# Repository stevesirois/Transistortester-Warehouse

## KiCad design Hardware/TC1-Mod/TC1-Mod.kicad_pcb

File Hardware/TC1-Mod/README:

------------------------------------------------------------------------------

  Modification for Multifunction Tester TC-1

  (c) 2018 by Markus Reschke (madires@theca-tabellaria.de)

------------------------------------------------------------------------------

The TC-1 Transistor Tester clone uses an additional small MCU for controlling
the power supply causing an incompatibilty with the open source k and
m-firmware. This small circuit is meant to replace the control MCU U4 to
be able to run the open source firmware. I'd recommend to glue the tiny
PCB of the replacement circuit to the main PCB using hot glue, and to connect
U4's pads with thin enamel wire (magnet wire). Please see the included
pictures for an inspiration ;)

PS: Remove the Li-Ion battery during the modifaction to prevent any damage.

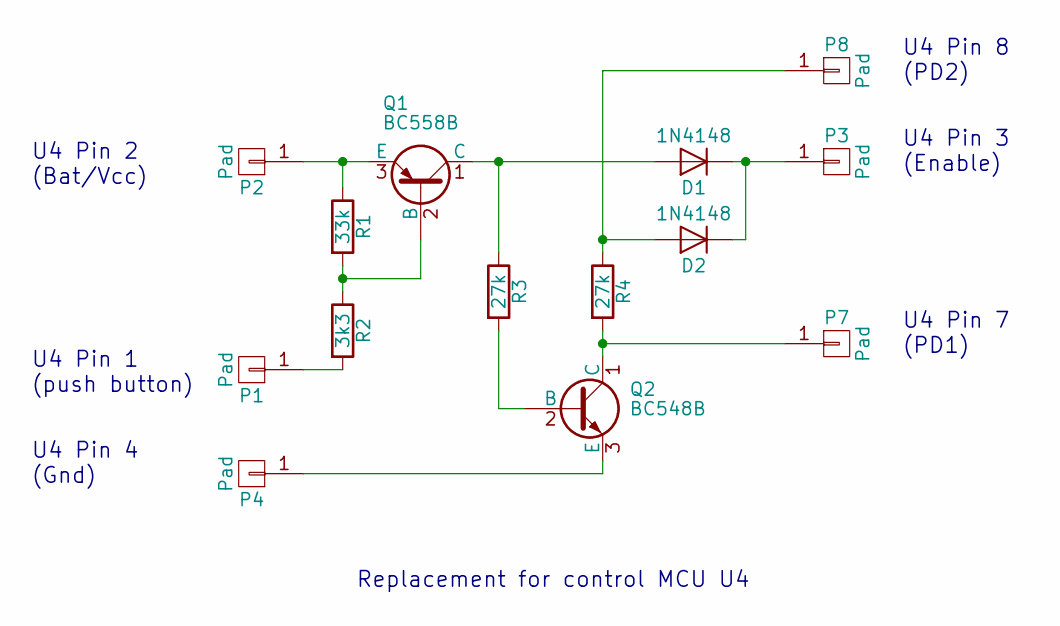
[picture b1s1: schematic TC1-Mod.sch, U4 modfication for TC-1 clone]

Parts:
D1, D2: 1N4148; Diode_DO-41_SOD81_Vertical_AnodeUp
P1, P2, P3, P4, P7, P8: Pad
Q1: BC558B; TO-92_Molded_Narrow_Oval
Q2: BC548B; TO-92_Molded_Narrow_Oval
R1: 33k; Resistor_Vertical_RM3.8mm
R2: 3k3; Resistor_Vertical_RM3.8mm
R3, R4: 27k; Resistor_Vertical_RM3.8mm

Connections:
unnamed: D1.1 (K), D2.1 (K), P3.1
unnamed: D1.2 (A), Q1.1 (C), R3.1
unnamed: D2.2 (A), P8.1, R4.1
unnamed: P1.1, R2.2
unnamed: P2.1, Q1.3 (E), R1.1
unnamed: P4.1, Q2.3 (E)
unnamed: P7.1, Q2.1 (C), R4.2
unnamed: Q1.2 (B), R1.2, R2.1
unnamed: Q2.2 (B), R3.2

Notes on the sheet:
U4 Pin 1 (push button)
U4 Pin 2 (Bat/Vcc)
U4 Pin 4 (Gnd)
U4 Pin 3 (Enable)
U4 Pin 7 (PD1)
U4 Pin 8 (PD2)
Replacement for control MCU U4

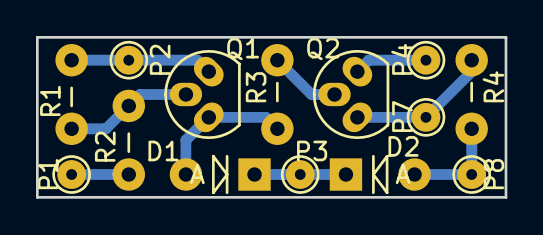
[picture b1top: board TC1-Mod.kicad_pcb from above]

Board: 2 copper layers, 26.0 x 8.9 mm, 14 parts (0 on the bottom side), 9 nets.

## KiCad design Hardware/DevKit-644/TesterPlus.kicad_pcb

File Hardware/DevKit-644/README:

------------------------------------------------------------------------------

  Component Tester Dev Kit with ATmega644/1284

  (c) 2021 by Markus Reschke (madires@theca-tabellaria.de)

------------------------------------------------------------------------------

Last edit:  2021-08-09

* About

The Component Tester is based on the project of Markus Frejek [1&2] and the
successor of Karl-Heinz Kübbeler [3&4].

* Safety Advice

The Component Tester is no DMM! It's a simple tester for components capable
of measuring several things. The probes aren't protected in any way and
won't survive higher voltages than 5V. Don't use the tester for live circuits!
Just use it for unsoldered electronic components! If you test a capacitor make
sure it's discharged before connecting the probes. This isn't just the Safety
Sally, your life may be at risk if you connect the probes to a live circuit
or a power supply (or even mains). 

* What's in the box?

Following files are in the archive:
- this README
- schematics as PDF
- schematics and PCB layout in KiCad v5 format 

* Circuit

The circuit is meant as development kit for writing and testing firmware.
It comes with the basic tester (without display) and:
- weak input protection
- 2.5 V voltage reference
- rotary encoder
- boost converter for Zener check
- fixed self-adjustment cap
- fixed cap and relay for k-firmware's SamplingADC
- pin header for displays and hardware options

* Layout

The layout is optimized for home lab PCB production without through-hole
plating. I recommend to use precision sockets for the ICs. They allow to solder
the pins at the top layer without much trouble. You might need to grind the top
layer pads for the crystal to prevent any short circuit of the leads via the
metal case.

* References

[1] AVR-Transistortester, Markus Frejek,
    Embedded Projects Journal, 2011-11

[2] http://www.mikrocontroller.net/topic/131804
    thread of Markus Frejek, Forum, 2009

[3] http://www.mikrocontroller.net/articles/AVR-Transistortester
    Online documentation of the Transistortester, Online Article, 2009-2011

[4] http://www.mikrocontroller.net/articles/AVR_Transistortester
    Short description of the TransistorTester, Karl-Heinz Kübbeler,
    Online Article, 2012

------------------------------------ EOF -------------------------------------

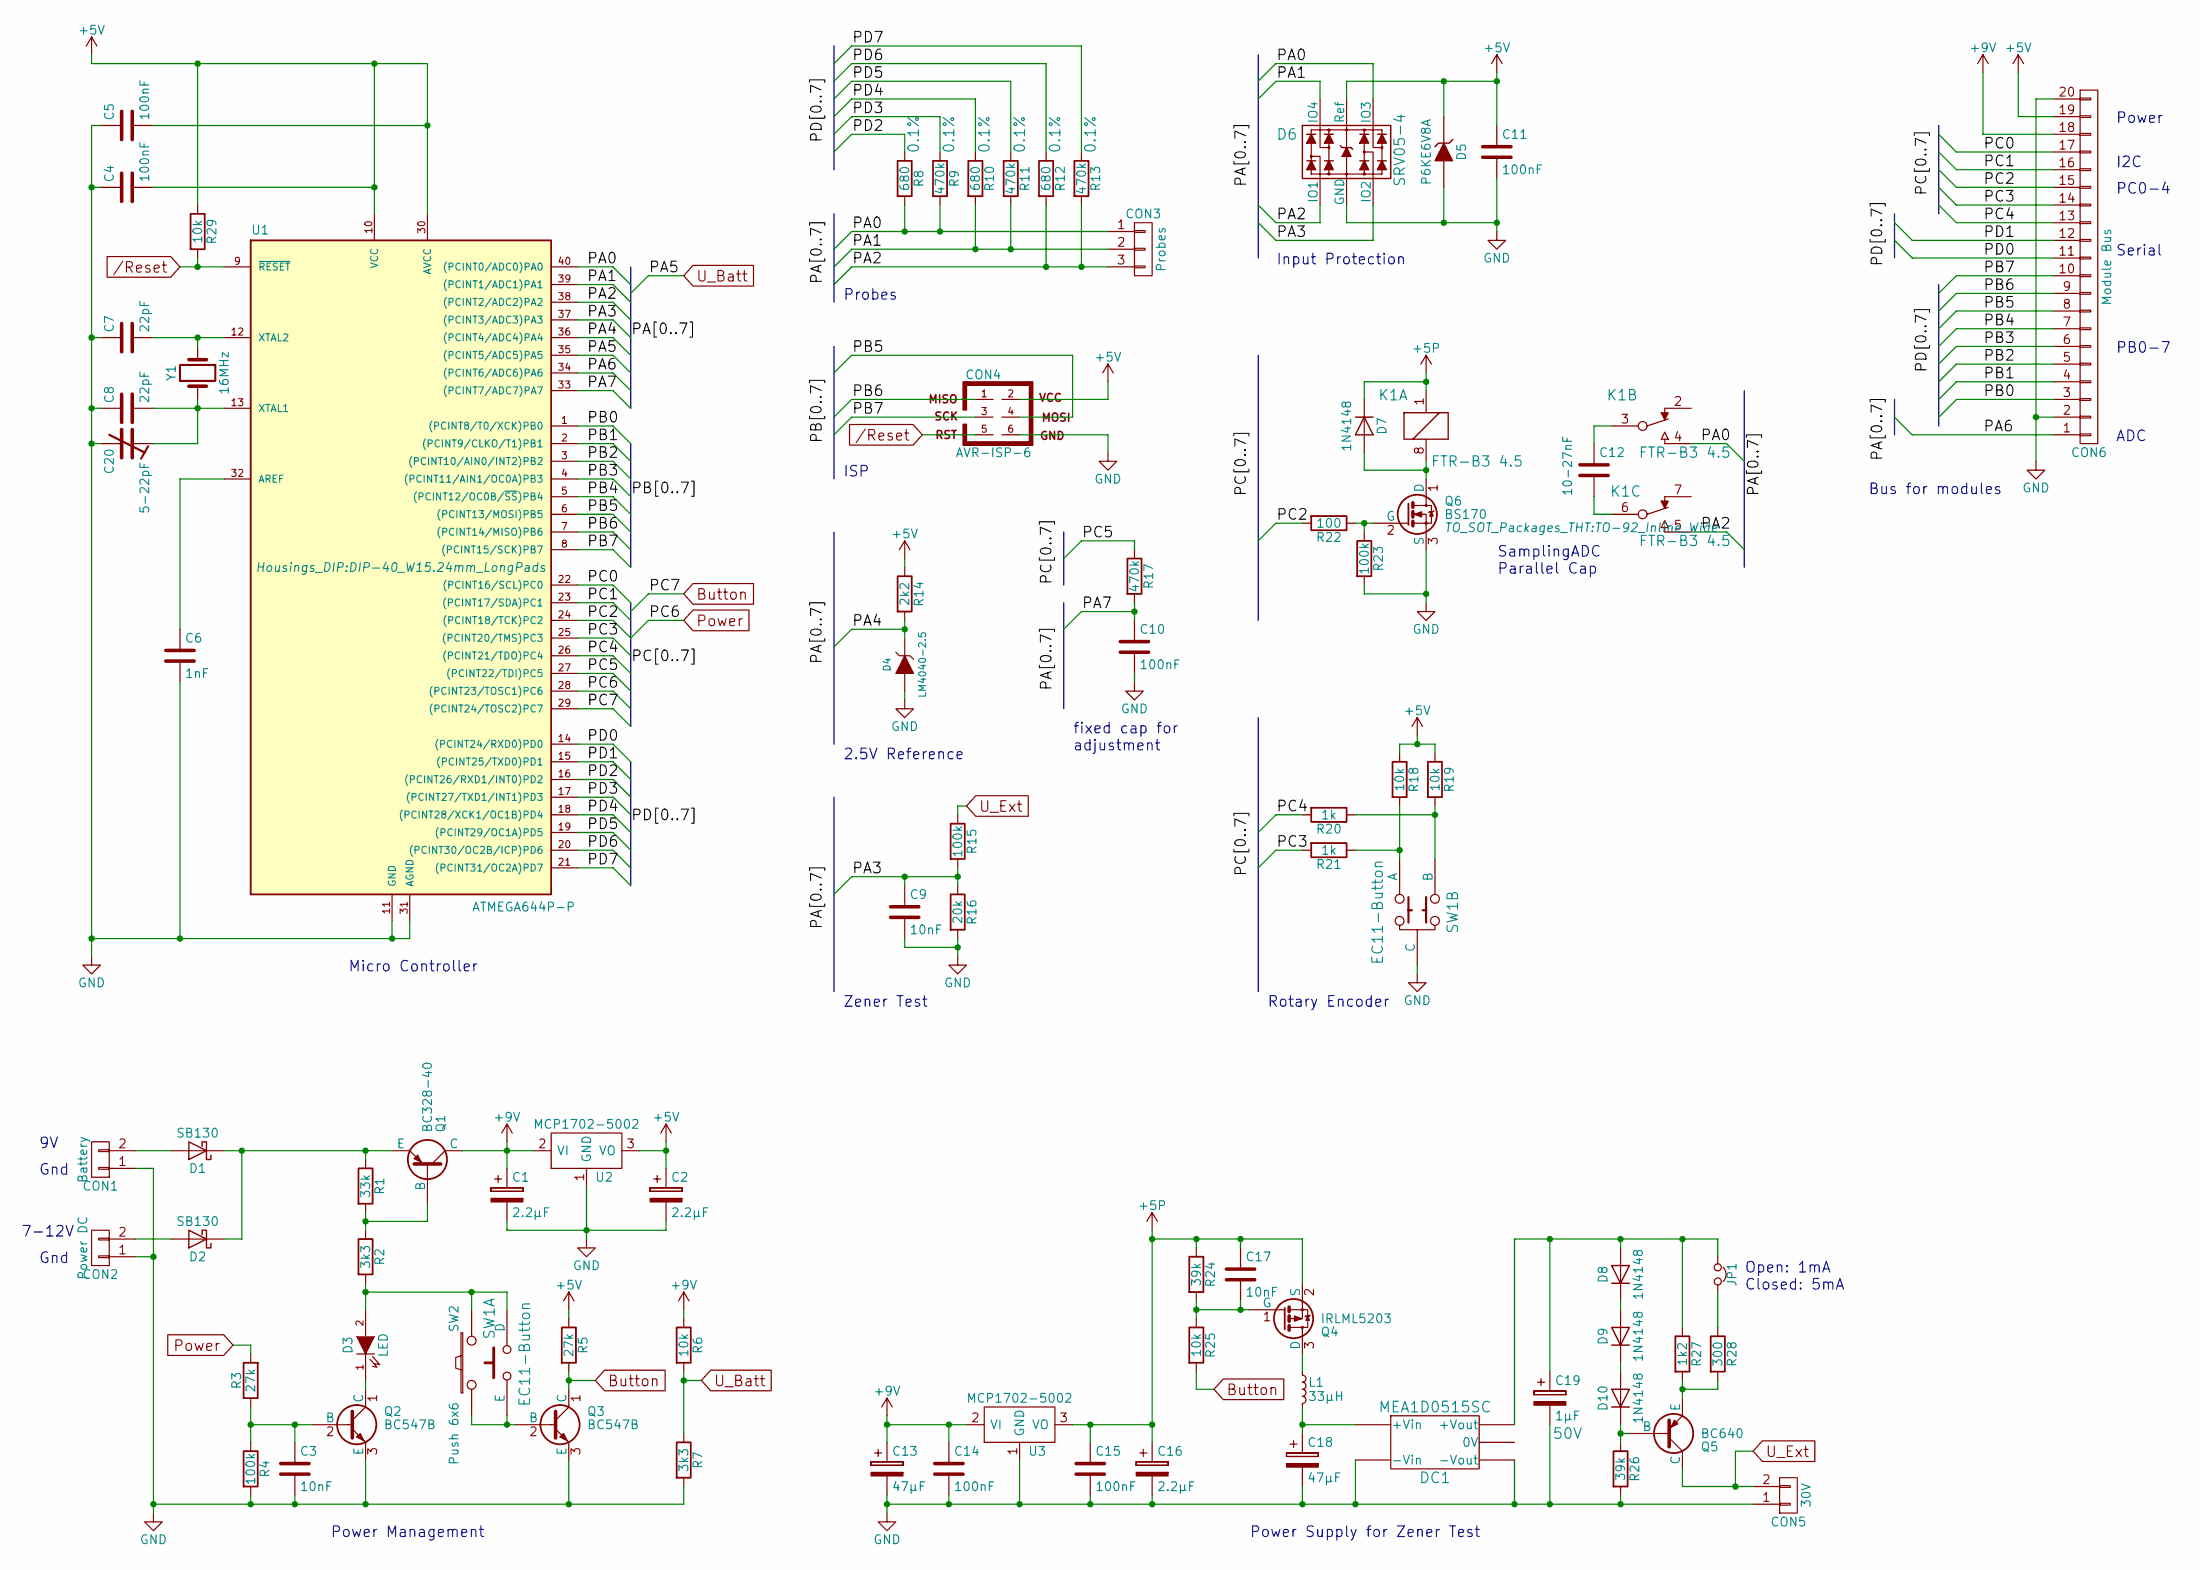
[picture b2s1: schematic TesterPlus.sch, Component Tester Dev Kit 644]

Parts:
C1, C2, C16: 2.2µF; C_Radial_D5_L11_P2.5
C3, C9, C17: 10nF; C_Rect_L7_W2_P5
C4, C5, C10, C11, C14, C15: 100nF; C_Rect_L7_W2_P5
C6: 1nF; C_Rect_L7_W2_P5
C7, C8: 22pF; C_Rect_L4_W2.5_P2.5
C12: 10-27nF; C_Rect_L7_W2_P5
C13, C18: 47µF; C_Radial_D10_L13_P5
C19: 1µF; C_Radial_D5_L11_P2.5; Voltage 50V
C20: 5-22pF; Trimmer-Cap-6mm-2p
CON1: Battery; Pin_Header_Straight_1x02
CON2: Power DC; Pin_Header_Straight_1x02
CON3: Probes; Pin_Header_Straight_1x03
CON4: AVR-ISP-6; Pin_Header_Straight_2x03
CON5: 30V; Pin_Header_Straight_1x02
CON6: Module Bus; Socket_Strip_Angled_1x20
D1, D2: SB130; Diode_DO-41_SOD81_Vertical_KathodeUp
D3: LED; LED-3MM
D4: LM4040-2.5; TO-92_Inline_Wide
D5: P6KE6V8A; Diode_P600_Vertical_KathodeUp
D6: SRV05-4; SOT-23-6
D7, D8, D9, D10: 1N4148; Diode_DO-35_SOD27_Horizontal_RM10
DC1: MEA1D0515SC; NMA-Series-SIP
JP1: I_max; Pin_Header_Straight_1x02
K1: FTR-B3 4.5; FTR-B3_TH; Coil Voltage ?V
L1: 33µH; Choke_Horizontal_RM15mm
Q1: BC328-40; TO-92_Molded_Narrow_Oval
Q2: BC547B; TO-92_Molded_Narrow_Oval
Q3: BC547B; TO-92_Inline_Wide
Q4: IRLML5203; SOT-23_Handsoldering
Q5: BC640; TO-92_Molded_Narrow_Oval
Q6: BS170; TO-92_Inline_Wide
R1: 33k; Resistor_Horizontal_RM10mm
R2, R7: 3k3; Resistor_Horizontal_RM10mm
R3, R5: 27k; Resistor_Horizontal_RM10mm
R4, R15, R23: 100k; Resistor_Horizontal_RM10mm
R6, R18, R19, R29: 10k; Resistor_Horizontal_RM10mm
R8, R10, R12: 680; Resistor_Horizontal_RM10mm; Tolerance 0.1%
R9, R11, R13: 470k; Resistor_Horizontal_RM10mm; Tolerance 0.1%
R14: 2k2; Resistor_Horizontal_RM10mm
R16: 20k; Resistor_Horizontal_RM10mm
R17: 470k; Resistor_Horizontal_RM10mm
R20, R21: 1k; Resistor_Horizontal_RM10mm
R22: 100; Resistor_Horizontal_RM10mm
R24, R26: 39k; Resistor_Vertical_RM5mm
R25: 10k; Resistor_Vertical_RM5mm
R27: 1k2; Resistor_Vertical_RM5mm
R28: 300; Resistor_Vertical_RM5mm
SW1: EC11-Button; EC11-Button-Vertical
SW2: Push 6x6; SW_PUSH_SMALL
U1: ATMEGA644P-P; DIP-40_W15.24mm_LongPads
U2, U3: MCP1702-5002; TO-92_Inline_Wide
Y1: 16MHz; Crystal_HC49-U_Vertical

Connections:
+5P: C15.1, C16.1, C17.1, D7.1 (K), K1.1 (A1), Q4.2 (S), R24.1, U3.3 (VO)
+5V: C2.1, C4.2, C5.2, C11.1, CON4.2, CON6.19, D5.1 (K), D6.5 (Ref), R5.1, R14.1, R18.1, R19.1, R29.1, U1.10 (VCC), U1.30 (AVCC), U2.3 (VO)
+9V: C1.1, C13.1, C14.1, CON6.18, Q1.1 (C), R6.1, U2.2 (VI), U3.2 (VI)
/PA0: CON3.1, D6.4 (IO3), K1.4 (NO), R8.2, R9.2, U1.40 ((PCINT0/ADC0)PA0)
/PA1: CON3.2, D6.6 (IO4), R10.2, R11.2, U1.39 ((PCINT1/ADC1)PA1)
/PA2: CON3.3, D6.1 (IO1), K1.5 (NO), R12.2, R13.2, U1.38 ((PCINT2/ADC2)PA2)
/PA3: C9.1, D6.3 (IO2), R15.2, R16.1, U1.37 ((PCINT3/ADC3)PA3)
/PA4: D4.2 (K), R14.2, U1.36 ((PCINT4/ADC4)PA4)
/PA6: CON6.1, U1.34 ((PCINT6/ADC6)PA6)
/PA7: C10.1, R17.2, U1.33 ((PCINT7/ADC7)PA7)
/PB0: CON6.3, U1.1 ((PCINT8/T0/XCK)PB0)
/PB1: CON6.4, U1.2 ((PCINT9/CLKO/T1)PB1)
/PB2: CON6.5, U1.3 ((PCINT10/AIN0/INT2)PB2)
/PB3: CON6.6, U1.4 ((PCINT11/AIN1/OC0A)PB3)
/PB4: CON6.7, U1.5 ((PCINT12/OC0B/~SS~)PB4)
/PB5: CON4.4, CON6.8, U1.6 ((PCINT13/MOSI)PB5)
/PB6: CON4.1, CON6.9, U1.7 ((PCINT14/MISO)PB6)
/PB7: CON4.3, CON6.10, U1.8 ((PCINT15/SCK)PB7)
/PC0: CON6.17, U1.22 ((PCINT16/SCL)PC0)
/PC1: CON6.16, U1.23 ((PCINT17/SDA)PC1)
/PC2: CON6.15, R22.2, U1.24 ((PCINT18/TCK)PC2)
/PC3: CON6.14, R21.2, U1.25 ((PCINT20/TMS)PC3)
/PC4: CON6.13, R20.2, U1.26 ((PCINT21/TDO)PC4)
/PC5: R17.1, U1.27 ((PCINT22/TDI)PC5)
/PD0: CON6.11, U1.14 ((PCINT24/RXD0)PD0)
/PD1: CON6.12, U1.15 ((PCINT25/TXD0)PD1)
/PD2: R8.1, U1.16 ((PCINT26/RXD1/INT0)PD2)
/PD3: R9.1, U1.17 ((PCINT27/TXD1/INT1)PD3)
/PD4: R10.1, U1.18 ((PCINT28/XCK1/OC1B)PD4)
/PD5: R11.1, U1.19 ((PCINT29/OC1A)PD5)
/PD6: R12.1, U1.20 ((PCINT30/OC2B/ICP)PD6)
/PD7: R13.1, U1.21 ((PCINT31/OC2A)PD7)
/Reset: CON4.5, R29.2, U1.9 (~RESET)
Button: Q3.1 (C), R5.2, R25.2, U1.29 ((PCINT24/TOSC2)PC7)
GND: C1.2, C2.2, C3.2, C4.1, C5.1, C6.2, C7.1, C8.1, C9.2, C10.2, C11.2, C13.2, C14.2, C15.2, C16.2, C18.2, C19.2, C20.2, CON1.1, CON2.1, CON4.6, CON5.1, CON6.2, CON6.20, D4.3 (A), D5.2 (A), D6.2 (GND), DC1.2 (-Vin), DC1.4 (-Vout), Q2.3 (E), Q3.3 (E), Q6.3 (S), R4.2, R7.2, R16.2, R23.2, R26.2, SW1.C, U1.11 (GND), U1.31 (AGND), U2.1 (GND), U3.1 (GND)
unnamed: C3.1, Q2.2 (B), R3.1, R4.1
unnamed: C6.1, U1.32 (AREF)
unnamed: C7.2, U1.12 (XTAL2), Y1.2
unnamed: C12.1, K1.3 (COM)
unnamed: C12.2, K1.6 (COM)
unnamed: C17.2, Q4.1 (G), R24.2, R25.1
unnamed: C18.1, DC1.1 (+Vin), L1.2
unnamed: C19.1, D8.2 (A), DC1.6 (+Vout), JP1.1, R27.1
unnamed: C8.2, C20.1, U1.13 (XTAL1), Y1.1
unnamed: CON1.2, D1.2 (A)
unnamed: CON2.2, D2.2 (A)
unnamed: D1.1 (K), D2.1 (K), Q1.3 (E), R1.1
unnamed: D3.1 (K), Q2.1 (C)
unnamed: D3.2 (A), R2.2, SW1.D, SW2.2
unnamed: D7.2 (A), K1.8 (A2), Q6.1 (D)
unnamed: D8.1 (K), D9.2 (A)
unnamed: D10.1 (K), Q5.3 (B), R26.1
unnamed: D9.1 (K), D10.2 (A)
unnamed: JP1.2, R28.1
unnamed: L1.1, Q4.3 (D)
unnamed: Q1.2 (B), R1.2, R2.1
unnamed: Q3.2 (B), SW1.E, SW2.1
unnamed: Q5.1 (E), R27.2, R28.2
unnamed: Q6.2 (G), R22.1, R23.1
unnamed: R18.2, R21.1, SW1.A
unnamed: R19.2, R20.1, SW1.B
Power: R3.2, U1.28 ((PCINT23/TOSC1)PC6)
U_Batt: R6.2, R7.1, U1.35 ((PCINT5/ADC5)PA5)
U_Ext: CON5.2, Q5.2 (C), R15.1

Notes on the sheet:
Gnd
7-12V
2.5V Reference
Probes
ISP
Zener Test
fixed cap for adjustment
SamplingADC Parallel Cap
Open: 1mA Closed: 5mA
Power Supply for Zener Test
Power Management
Micro Controller
Rotary Encoder
Input Protection
Power
I2C
PC0-4
PB0-7
ADC
Serial
Bus for modules

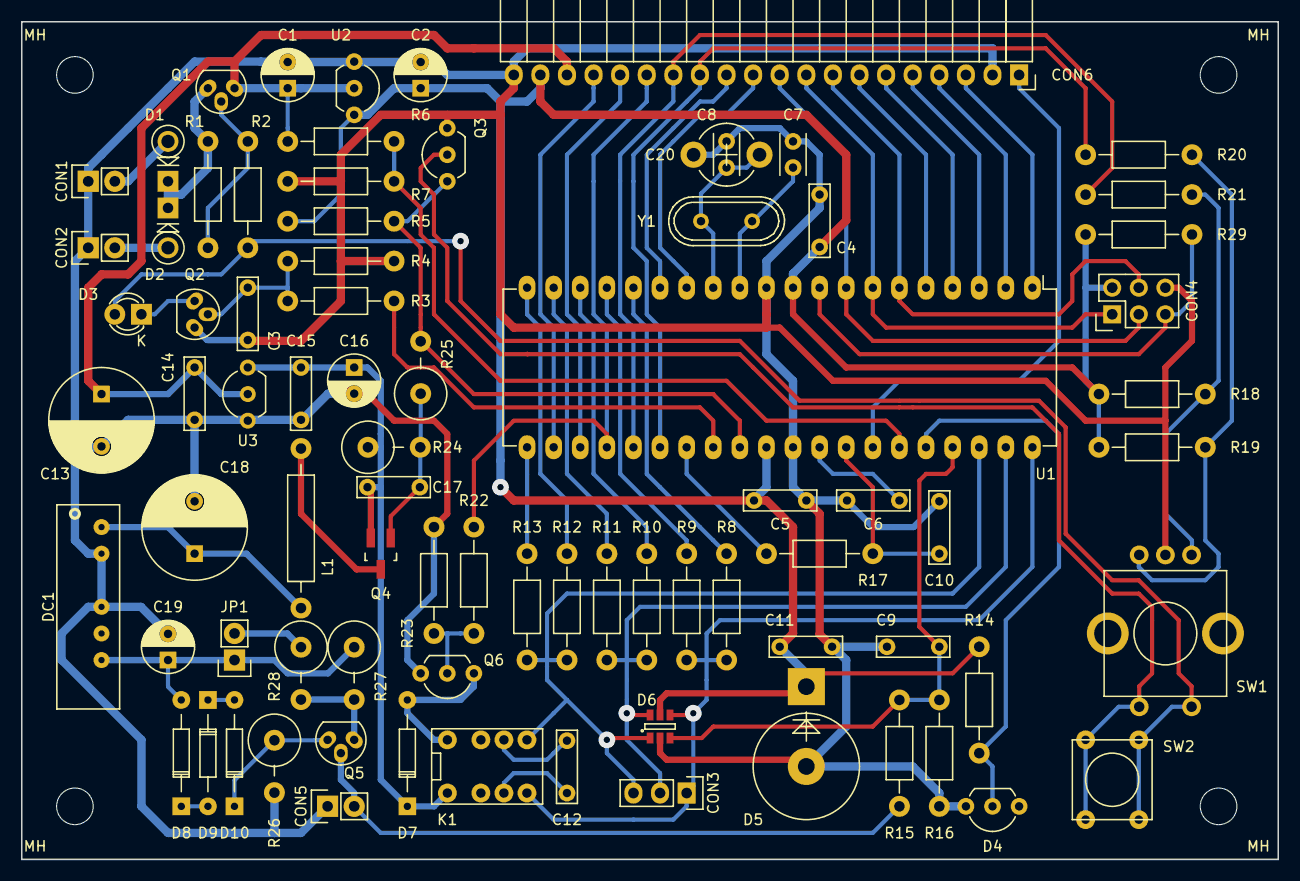
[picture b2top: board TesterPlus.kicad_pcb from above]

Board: 2 copper layers, 120.0 x 80.0 mm, 85 parts (0 on the bottom side), 64 nets.

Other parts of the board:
MH: 3.5mm; MountingHole_3-5mm
MH#2, MH#3, MH#4: 3.5mm; MountingHole_3-5mm

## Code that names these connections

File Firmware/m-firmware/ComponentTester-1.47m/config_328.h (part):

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#define LCD_PORT         PORTD          /* port data register */
#define LCD_DDR          DDRD           /* port data direction register */
#define LCD_DB_STD                      /* use standard pins 0-3 for DB4-7 */
#define LCD_DB4          PD0            /* port pin used for DB4 */
#define LCD_DB5          PD1            /* port pin used for DB5 */
#define LCD_DB6          PD2            /* port pin used for DB6 */
#define LCD_DB7          PD3            /* port pin used for DB7 */
#define LCD_RS           PD4            /* port pin used for RS */
#define LCD_EN1          PD5            /* port pin used for E */
/* display settings */
#define LCD_CHAR_X       16             /* characters per line */
#define LCD_CHAR_Y       2              /* number of lines */
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#define I2C_PORT         PORTD          /* I2C port data register */
#define I2C_DDR          DDRD           /* I2C port data direction register */
#define I2C_PIN          PIND           /* I2C port input pins register */
#define I2C_SDA          PD0            /* port pin used for SDA */
#define I2C_SCL          PD1            /* port pin used for SCL */
#endif


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/* control and data lines */
#define LCD_PORT         PORTD          /* port data register */
#define LCD_DDR          DDRD           /* port data direction register */
#define LCD_RES          PD4            /* port pin used for /RESX (optional) */
#define LCD_CS           PD5            /* port pin used for /CSX (optional) */
#define LCD_DC           PD3            /* port pin used for D/CX */
#define LCD_SCL          PD2            /* port pin used for SCL */
#define LCD_SDA          PD1            /* port pin used for SDA/SDIO */
/* display settings */
#define LCD_DOTS_X       128            /* number of horizontal dots */
#define LCD_DOTS_Y       128            /* number of vertical dots */
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/* control and data lines */
#define LCD_PORT         PORTD          /* port data register */
#define LCD_DDR          DDRD           /* port data direction register */
#define LCD_RES          PD4            /* port pin used for /RES (optional) */
#define LCD_CS           PD5            /* port pin used for /CS (optional) */
#define LCD_DC           PD3            /* port pin used for D/C */
#define LCD_SCK          PD2            /* port pin used for SCK */
#define LCD_SDI          PD1            /* port pin used for SDI (data input) */
//#define LCD_SDO          PD0            /* port pin used for SDO (data output) */
/* display settings */
#define LCD_DOTS_X       320            /* number of horizontal dots */
#define LCD_DOTS_Y       240            /* number of vertical dots */
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/* control and data lines */
#define LCD_PORT         PORTD          /* port data register */
#define LCD_DDR          DDRD           /* port data direction register */
#define LCD_RES          PD4            /* port pin used for /RES (optional) */
#define LCD_SCE          PD5            /* port pin used for /SCE (optional) */
#define LCD_DC           PD3            /* port pin used for D/C */
#define LCD_SCLK         PD2            /* port pin used for SCLK */
#define LCD_SDIN         PD1            /* port pin used for SDIN (data input) */
/* display settings */
#define LCD_DOTS_X       84             /* number of horizontal dots */
#define LCD_DOTS_Y       48             /* number of vertical dots */
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/* control and data lines */
#define LCD_PORT         PORTD          /* port data register */
#define LCD_DDR          DDRD           /* port data direction register */
#define LCD_RESET        PD4            /* port pin used for /RES */
#define LCD_CS           PD5            /* port pin used for /CS (optional) */
#define LCD_SCLK         PD2            /* port pin used for SCLK */
#define LCD_SDIN         PD1            /* port pin used for SDIN (data input) */
/* display settings */
#define LCD_DOTS_X       96             /* number of horizontal dots */
#define LCD_DOTS_Y       65             /* number of vertical dots */
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/* control and data lines */
#define LCD_PORT         PORTD          /* port data register */
#define LCD_DDR          DDRD           /* port data direction register */
#define LCD_RESET        PD4            /* port pin used for /RES (optional) */
#define LCD_CS           PD5            /* port pin used for /CS (optional) */
#define LCD_A0           PD3            /* port pin used for A0 */
#define LCD_SCL          PD2            /* port pin used for SCL */
#define LCD_SI           PD1            /* port pin used for SI (data input) */
/* display settings */
#define LCD_DOTS_X       128            /* number of horizontal dots */
#define LCD_DOTS_Y       64             /* number of vertical dots */
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/* control and data lines */
#define LCD_PORT         PORTD          /* port data register */
#define LCD_DDR          DDRD           /* port data direction register */
#define LCD_RESET        PD4            /* port pin used for /RES (optional) */
#define LCD_CS           PD5            /* port pin used for /CS (optional) */
#define LCD_SCL          PD2            /* port pin used for SCL */
#define LCD_SI           PD1            /* port pin used for SI (data input) */
/* display settings */
#define LCD_DOTS_X       128            /* number of horizontal dots */
#define LCD_DOTS_Y       64             /* number of vertical dots */
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/* control lines */
#define LCD_PORT         PORTD          /* port data register */
#define LCD_DDR          DDRD           /* port data direction register */
//#define LCD_RESET        PD4            /* port pin used for /RES (optional) */
/* display settings */
#define LCD_DOTS_X       128            /* number of horizontal dots */
#define LCD_DOTS_Y       64             /* number of vertical dots */
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#define I2C_PORT         PORTD          /* I2C port data register */
#define I2C_DDR          DDRD           /* I2C port data direction register */
#define I2C_PIN          PIND           /* I2C port input pins register */
#define I2C_SDA          PD0            /* port pin used for SDA */
#define I2C_SCL          PD1            /* port pin used for SCL */
#endif


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/* control and data lines */
#define LCD_PORT         PORTD          /* port data register */
#define LCD_DDR          DDRD           /* port data direction register */
#define LCD_RESET        PD4            /* port pin used for /RES (optional) */
#define LCD_CS           PD5            /* port pin used for /CS (optional) */
#define LCD_DC           PD3            /* port pin used for D/C */
#define LCD_SCLK         PD2            /* port pin used for SCLK */
#define LCD_SDIN         PD1            /* port pin used for SDIN (data input) */
/* display settings */
#define LCD_DOTS_X       128            /* number of horizontal dots */
#define LCD_DOTS_Y       64             /* number of vertical dots */
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/* control and data lines */
#define LCD_PORT         PORTD          /* port data register */
#define LCD_DDR          DDRD           /* port data direction register */
#define LCD_RESET        PD4            /* port pin used for /RES (optional) */
#define LCD_CS           PD5            /* port pin used for /CS (optional) */
#define LCD_SCLK         PD2            /* port pin used for SCLK */
#define LCD_SDIN         PD1            /* port pin used for SDIN (data input) */
/* display settings */
#define LCD_DOTS_X       128            /* number of horizontal dots */
#define LCD_DOTS_Y       64             /* number of vertical dots */
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/* control lines */
#define LCD_PORT         PORTD          /* port data register */
#define LCD_DDR          DDRD           /* port data direction register */
#define LCD_RESET        PD4            /* port pin used for /RES (optional) */
/* display settings */
#define LCD_DOTS_X       128            /* number of horizontal dots */
#define LCD_DOTS_Y       64             /* number of vertical dots */
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#define I2C_PORT         PORTD          /* I2C port data register */
#define I2C_DDR          DDRD           /* I2C port data direction register */
#define I2C_PIN          PIND           /* I2C port input pins register */
#define I2C_SDA          PD0            /* port pin used for SDA */
#define I2C_SCL          PD1            /* port pin used for SCL */
#endif


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#define LCD_PORT         PORTD          /* port data register */
#define LCD_DDR          DDRD           /* port data direction register */
//#define LCD_DB_STD                      /* use standard pins 0-3 for DB4-7 */
#define LCD_DB4          PD0            /* port pin used for DB4 */
#define LCD_DB5          PD1            /* port pin used for DB5 */
#define LCD_DB6          PD2            /* port pin used for DB6 */
#define LCD_DB7          PD3            /* port pin used for DB7 */
#define LCD_RS           PD4            /* port pin used for RS */
#define LCD_EN           PD5            /* port pin used for E */
//#define LCD_RW           ???            /* port pin used for R/W (optional) */
//#define LCD_RESET        ???            /* port pin used for XRESET (optional) */
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
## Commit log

2024-09-21 checkout of v1.53
2024-09-21 beta version
2024-09-21 added power save for battery
2024-09-22 use inc dec button instead
2024-09-23 swap key button vs pcb layout
2024-09-23 new hex
2024-09-29 no v ref and 20 mhz
2024-09-30 chg voltage ref
2024-10-05 adjusted offset
2024-10-07 set avrdude -B parameter for new chip
2024-10-17 vbat divider ajusted

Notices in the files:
Firmware/m-firmware/ComponentTester-1.47m/config_328.h:
(c) 2012-2022 by Markus Reschke
